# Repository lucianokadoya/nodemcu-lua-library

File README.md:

# nodemcu-lua-library
Meccano Client Library for NodeMCU (lua)

# About Meccano IoT Project

Meccano project is a multi-purpose IoT (Internet of Things) board and software platform created by Luciano Kadoya, Rogério Biondi, Diego Osse and Talita Paschoini. Its development started in early 2014 as a closed R&D project in the Software Architecture Division, with the aim of creating a board which is robust, based on a modern microprocessor (ESP8266), cheap, easy to implement and deploy through the 750 retail stores to perform several functions, such as:

- Count the number of visitors in each store to calculate the sales/visits ratio;
- Get the vote/feedback of users regarding the services;
- Voice marketing;
- Energy saving initiatives;
- Beacons and interaction of the customer in the physical store;
- Several other undisclosed applications;

Different from other ESP8266 projects, Meccano board has been heavily tested in retail stores and adjusted to be safe against RF (radio frequency) interferences. The physical store is an inhospitable environment since there are several hundreds of electronic products, such as TVs, computers, sound and home theaters as well as electronic home appliances.

The project is still in its early stages and will evolve in the future. Magazine Luiza will plan the backlog and sponsor the project. It has been open-sourced because it´s the first initiative to create a board based on ESP8266 in Brazil and we are really excited with the possibilities. Magazine Luiza has a passion for innovations and contribution to the development of technology. So you are invited to join us because your support/collaboration is welcome!

# NodeMCU-Lua-Library

Meccano nodemcu-lua-library is a client library for NodeMCU Using the Lua Firmware.

## Features:

 - Simple to use
 - Integration to Meccano Gateway    
    - Create and send facts
    - Check and execute messages from gateway

## Limitations:

- Due to the asynchronous nature of Lua in NodeMCU, the local persistence of data when connection is not available is not implemented yet.

- There is not enough memory, so if you want to have more room for creating your Lua program, we strongly recommend you build a custom firmware for NodeMCU. Minimum modules you should include: adc, file, gpio, net, node, tmr, wifi and the modules your program will use. In this site you may create it: http://nodemcu-build.com/

- No buzz and led functions yet (low memory).

## requirements

In order to use nodemcu-lua-library you should prepare and reflash your NodeMCU to use the latest version or use a custom firmware with just the modules you'll need (see the limitations above). More information about NodeMCU platform may be found on:

http://www.nodemcu.com

## Installation

1. Download the zip from GIT Hub to a local directory (e. g. Dowloads)
2. Rename file Downloads/node-lua-library-master.zip > node-lua-library
2. Open your IDE (we use the ESPlorer IDE - http://esp8266.ru/ )
3. Click the Upload Button and select the file node-lua-library/meccano.lua
4. Open the node-lua-library/example.lua, change it according your needs and Save/Run

### Mininum Meccano Program

You need to include the meccano library in your code:

```
-- Include meccano module
local meccano = require("meccano")

-- Contact the Meccano Network
meccano.setup("ssid", "ssid_password", "meccano-gateway-host", 80, function()
  -- Your main program
  print("My hook...")
  tmr.alarm(1, 100, 1,
    function()
      -- Your program here
      -- read gpio, adc port and so on

      -- If you need to create and send a fact
      fact = meccano.fact_create("feedback", 1, 100)
      meccano.fact_send(fact, function()
        print("Data successfuly sent!")
      end)
  end)
end)
```

### Functions

#### Setup functions ####

##### void setup(ssid, ssid_password, server, port, userfn) #####

The setup() will do the following functions:

1. Setup and get the device id (mac-address);
2. Setup the wifi connection to the access point (AP). You must provide your AP credentials (ssid and password);
3. Setup the connection to gateway. You must pass the host (or IP) and port where the meccano gateway is running;
4. It will register the device in the Meccano Network;
5. It will get the clock information.

```
meccano.setup("ssid", "passwd", "meccano.server.iot", 80, function()
  print("Connected to meccano network!")
  -- My program here
end)
```

#### Fact functions ####

Facts are the representation of a physical event. They are data captured by the sensors of Meccano Mini Board. It can be a temperature sensor, a line infrared or PIR sensor or others. The data of a fact is represented by a numeric value. Examples: for a temperature sensor it should be a number between -100 and 100 representing the celsius measure, or if you create a button it can be the number of times which it has been pressed by the user.

##### fact_create(channel, sensor, value) #####

When you create a fact, you must specify a channel. The channel is a class that identify which kind of information you want to send to the meccano gateway. Besides the channel, each fact must specify the sensor. You must define a number for each sensor connected to your meccano mini board. Let's consider, for example, that you have a PIR sensor connected in one port and a temperature sensor in other port. for identification, you should consider the PIR as sensor 1 and temperature as sensor 2. If you have several identical appliances which the same configuration, you must keep the same configuration of sensor for all devices. The value of the sensor is the data captured of them. This can be a value of temperature, a voltage or whatever you need to collect.

##### fact_send(String fact, userfn) #####

Send a fact to the meccano gateway.

```
fact = meccano.fact_create("my_channel", 1, 100)
meccano.fact_send(fact, function()
  print("Data sent to meccano network!")
end)
```

***
NOTE: There is no persistence for the facts in this first version, which means that the client operates only in on-line mode
***

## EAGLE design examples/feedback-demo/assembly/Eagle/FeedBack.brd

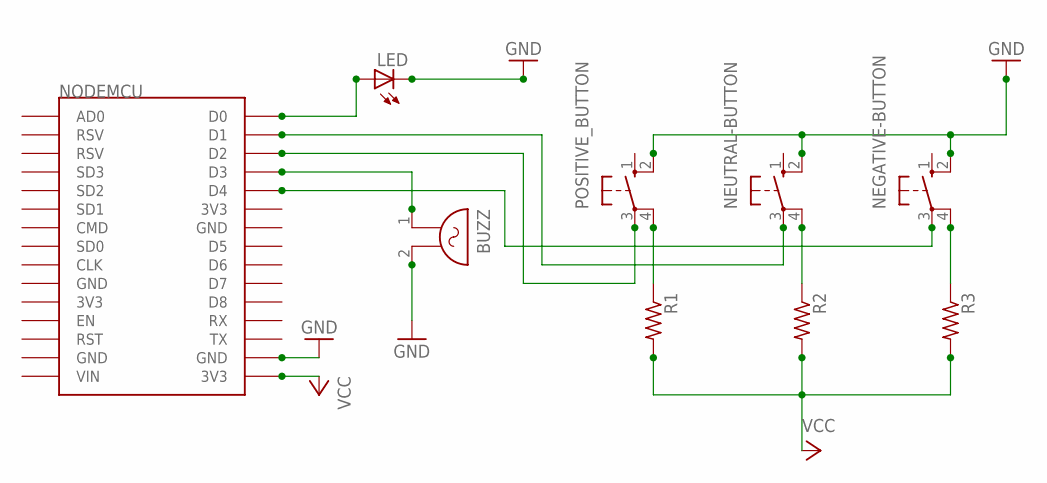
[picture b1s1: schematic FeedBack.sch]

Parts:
BUZZ: F/HGP
LED: LED3MM
NEGATIVE-BUTTON: 10-XX; B3F-10XX
NEUTRAL-BUTTON: 10-XX; B3F-10XX
NODEMCU: ESP12E_DEVKIT
POSITIVE_BUTTON: 10-XX; B3F-10XX
R1, R2, R3: R-US_0204/5; 0204/5

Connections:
GND: BUZZ.2, LED.K (C), NEGATIVE-BUTTON.2 (S1), NEUTRAL-BUTTON.2 (S1), NODEMCU.GND@3 (GND), POSITIVE_BUTTON.2 (S1)
unnamed: POSITIVE_BUTTON.4 (P1), R1.1
unnamed: NEUTRAL-BUTTON.4 (P1), R2.1
unnamed: NEGATIVE-BUTTON.4 (P1), R3.1
unnamed: BUZZ.1, NODEMCU.D3
unnamed: NEUTRAL-BUTTON.3, NODEMCU.D1
unnamed: NODEMCU.D2, POSITIVE_BUTTON.3
unnamed: NEGATIVE-BUTTON.3, NODEMCU.D4
unnamed: LED.A, NODEMCU.D0
VCC: NODEMCU.3V3@2 (3V3), R1.2, R2.2, R3.2

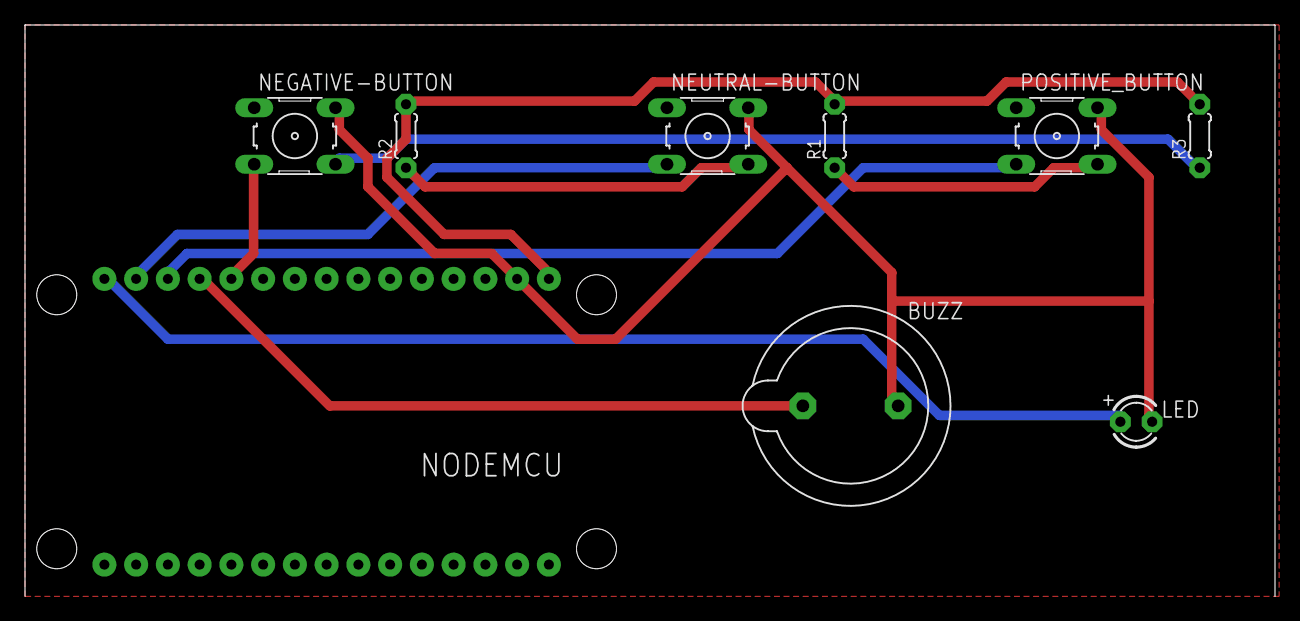
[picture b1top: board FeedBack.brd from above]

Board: 2 copper layers, 100.0 x 45.7 mm, 9 parts (0 on the bottom side), 10 nets.

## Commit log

2016-03-08 First version
2016-03-08 Removed message
2016-03-08 Debug adjustment
2016-03-08 Doc adjustment
2016-03-09 Removed debug messages
2016-03-09 User-Agent fix
2016-03-16 General fixes
2016-03-16 Feedback Demo
    Improvements for lua library: handling events with user functions.
    (sorry, I’m not a lua programmer!)
    Added customer feedback demo.
2016-03-22 Included Feedback Assembly Files
2016-03-22 Included Protoboard image
2016-04-06 Added new protobord photos
